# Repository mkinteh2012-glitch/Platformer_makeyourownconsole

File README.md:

# Pixel Player 8
Overview    
This is a console made and designed by @PenguinMo or Muhammad Kinteh for Hack Club's build your own console program 
This repo is organized into 5 sections.  
0. Overview
1. Pixel Platformer
2. Console Controller
3. Console Launcher
4. Console Design

Pixel Platformer 

Embark on an epic quest . . .     
This is pixel platformer a game designed in Godot 4 for the console, Pixel Player 8 this game is a platformer based off brackeye's tutorial 
You can play the game here: https://muhammad12412.itch.io/pixel-platformer 
Watch the walkthrough here: https://www.youtube.com/watch?v=EgpC5o8dRrM 
Screenshots:

2. Controller

So now u can play!        
This is a controller made by me and powered by the
This controller has the same layout as an Xbox 1 except no center button  
Screenshots: 

3. Launcher
The launcher for this is very simple it uses python and has good capabilities and is controller and arrow key compatable
This was made for .exe games making it possible to add other non godot games, Screenshots:     

4. Console
The console is povered by a mini PC and put is a case layout it hase foam for protection and holes can be cut in the case it hase speakers and everything needed

TIME BREAKDOWN: Game: 13h via hackatime Controller 14h via journal launcher 8 via hackatime Console 27 via journal Total: 60hx 5 = 300

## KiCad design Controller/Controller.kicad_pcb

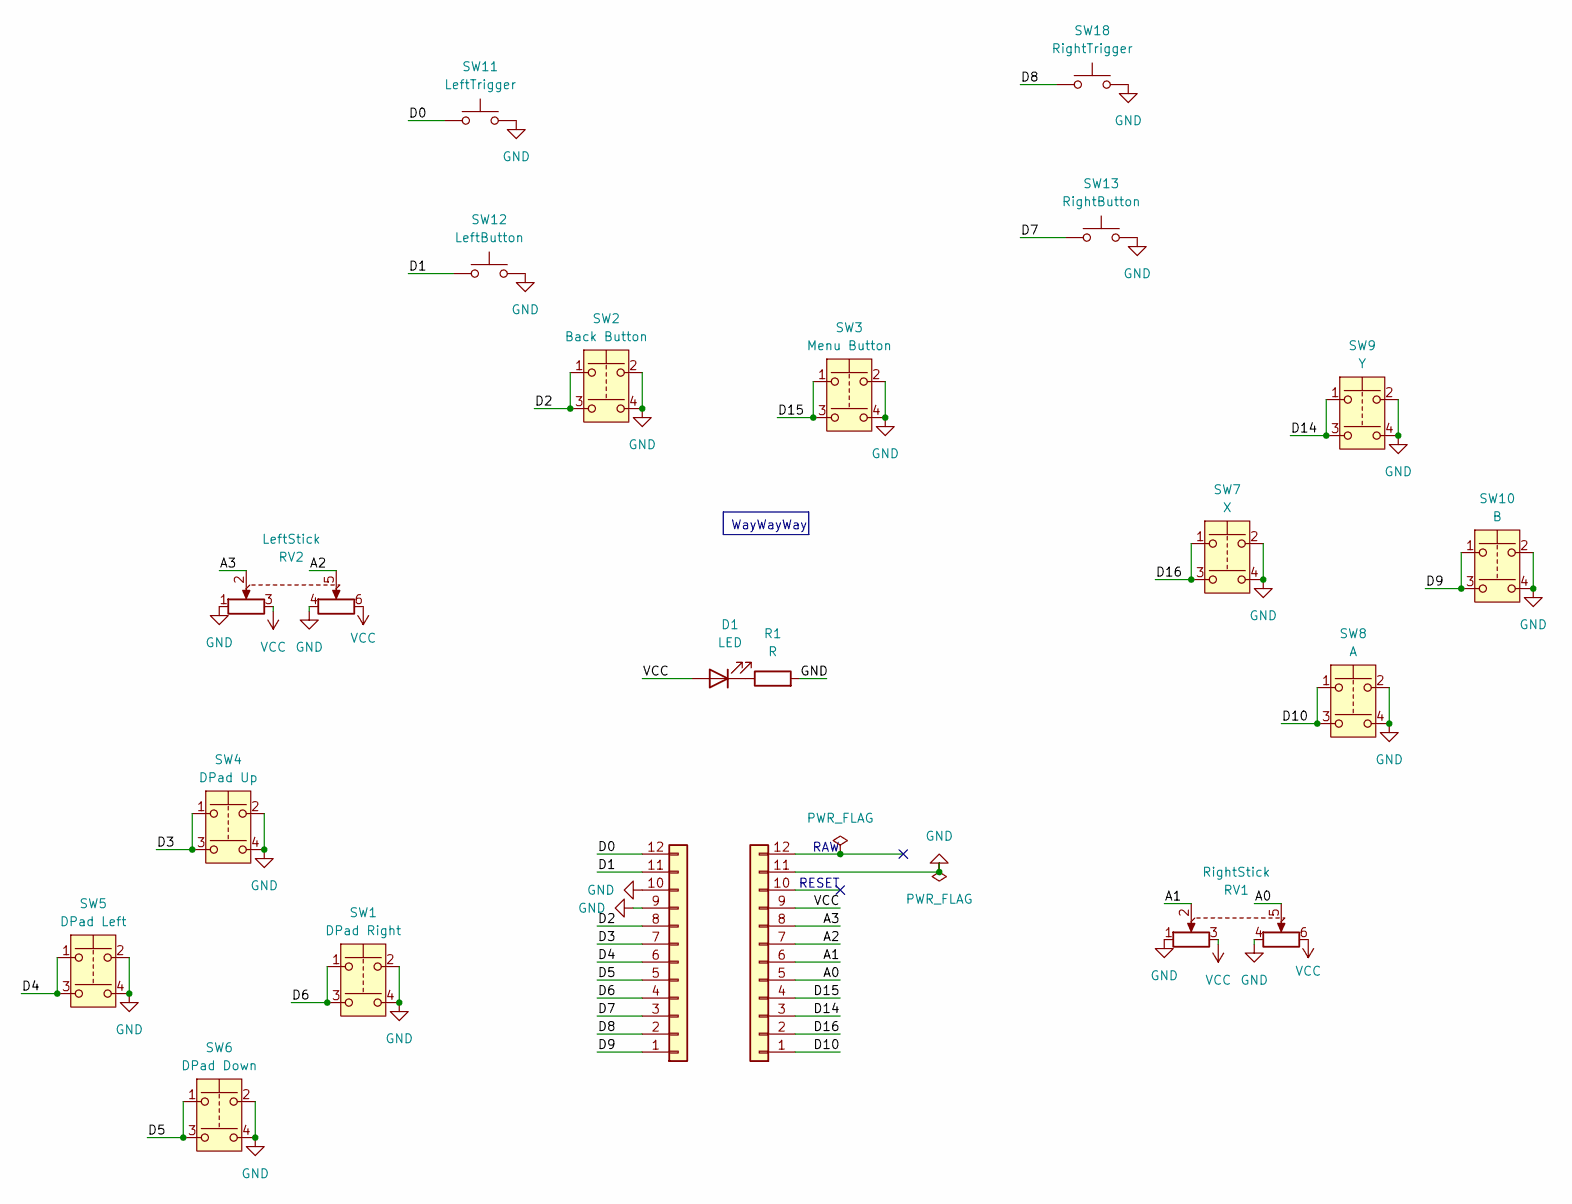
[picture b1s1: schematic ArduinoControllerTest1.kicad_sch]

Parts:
D1: LED; LED_D5.0mm
J3, J4: Conn_01x12; PinHeader_1x12_P2.54mm_Vertical
R1: R; R_Axial_DIN0207_L6.3mm_D2.5mm_P10.16mm_Horizontal
RV1: RightStick; JOYSTICK
RV2: LeftStick; JOYSTICK
SW1: DPad Right; Push_E-Switch_KS01Q01
SW2: Back Button; Push_E-Switch_KS01Q01
SW3: Menu Button; Push_E-Switch_KS01Q01
SW4: DPad Up; Push_E-Switch_KS01Q01
SW5: DPad Left; Push_E-Switch_KS01Q01
SW6: DPad Down; Push_E-Switch_KS01Q01
SW7: X; Push_E-Switch_KS01Q01
SW8: A; Push_E-Switch_KS01Q01
SW9: Y; Push_E-Switch_KS01Q01
SW10: B; Push_E-Switch_KS01Q01
SW11: LeftTrigger; SW_Tactile_SKHH_Angled
SW12: LeftButton; SW_Tactile_SKHH_Angled
SW13: RightButton; SW_Tactile_SKHH_Angled
SW18: RightTrigger; SW_Tactile_SKHH_Angled

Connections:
/A0: J3.5, RV1.5
/A1: J3.6, RV1.2
/A2: J3.7, RV2.5
/A3: J3.8, RV2.2
/D0: J4.12, SW11.1
/D1: J4.11, SW12.1
/D2: J4.8, SW2.1, SW2.3
/D3: J4.7, SW4.1, SW4.3
/D4: J4.6, SW5.1, SW5.3
/D5: J4.5, SW6.1, SW6.3
/D6: J4.4, SW1.1, SW1.3
/D7: J4.3, SW13.1
/D8: J4.2, SW18.1
/D9: J4.1, SW10.1, SW10.3
/D10: J3.1, SW8.1, SW8.3
/D14: J3.3, SW9.1, SW9.3
/D15: J3.4, SW3.1, SW3.3
/D16: J3.2, SW7.1, SW7.3
GND: J3.11, J4.9, J4.10, R1.2, RV1.1, RV1.4, RV2.1, RV2.4, SW1.2, SW1.4, SW2.2, SW2.4, SW3.2, SW3.4, SW4.2, SW4.4, SW5.2, SW5.4, SW6.2, SW6.4, SW7.2, SW7.4, SW8.2, SW8.4, SW9.2, SW9.4, SW10.2, SW10.4, SW11.2, SW12.2, SW13.2, SW18.2
unnamed: D1.1 (K), R1.1
VCC: D1.2 (A), J3.9, RV1.3, RV1.6, RV2.3, RV2.6

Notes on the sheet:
WayWayWay
RAW
RESET

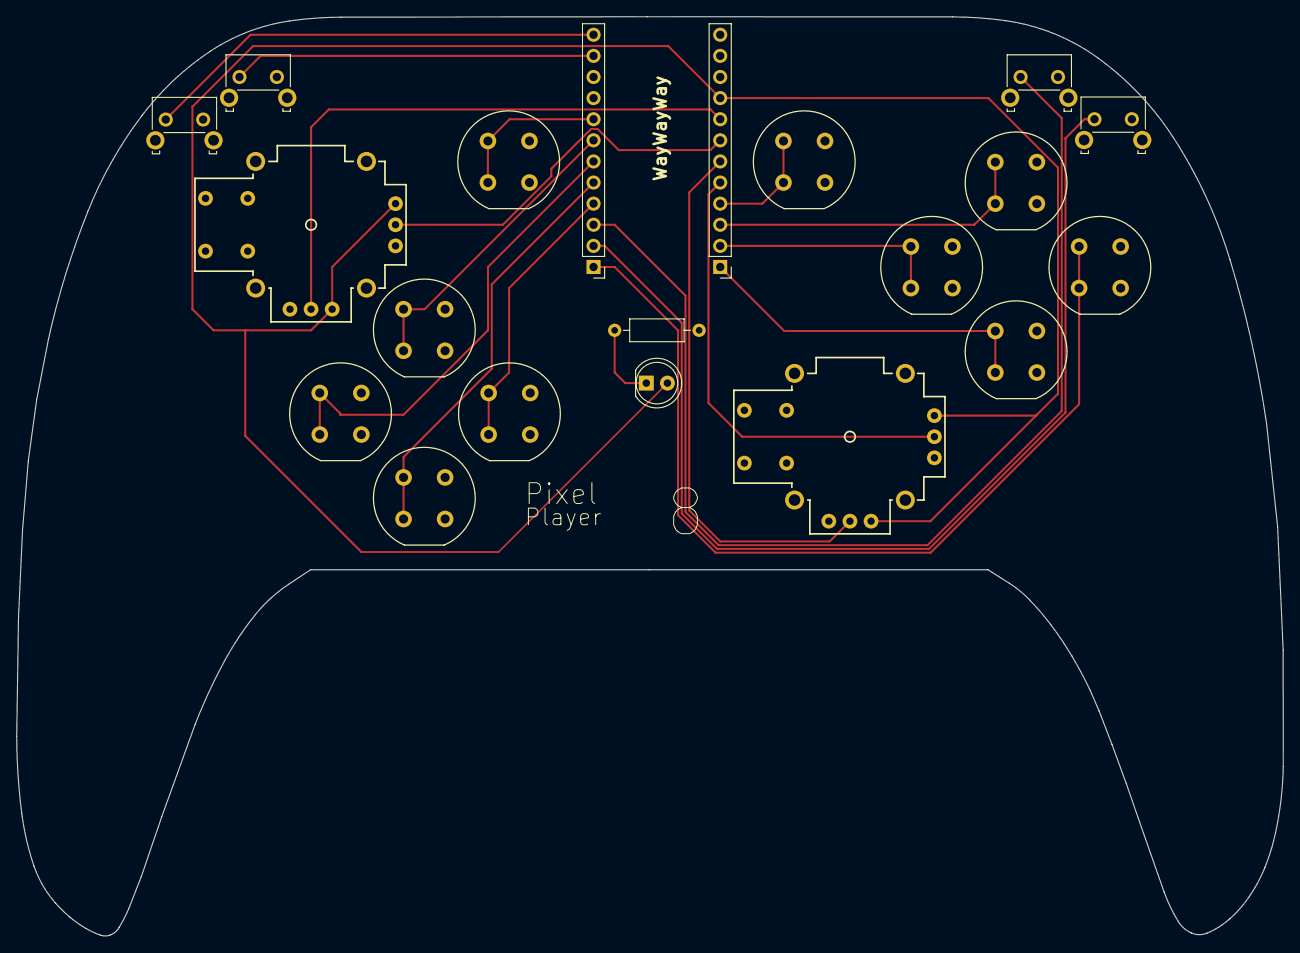
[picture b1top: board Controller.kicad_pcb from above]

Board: 2 copper layers, 152.4 x 110.6 mm, 20 parts (0 on the bottom side), 21 nets.

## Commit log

2026-01-08 Started added basic physics
2026-01-08 Organized project into Game folder
2026-01-08 Organized all project folders into Game directory
2026-01-08 Cleanup: Move metadata to root
2026-01-08 Began level design
2026-01-08 Added platform
2026-01-10 fixed death
2026-01-10 added slime
2026-01-10 added player animation
2026-01-11 added more level
2026-01-11 added more coins
2026-01-11 added bg
2026-01-12 now there is checkpints
2026-01-12 DONE
2026-01-12 Rename Console Game to Pixel Platformer
    Updated the README to reflect the new game title and added details about the Pixel Platformer.
2026-01-15 Revise README with project name and sections
    Updated README to include project name and details.
2026-01-15 Add journal entry on console design concept
    Added a new entry about console design ideas.
2026-01-17 Update Journal with project ideas and progress
    Added detailed entries about project progress and plans.
2026-01-17 Revise journal entry with PCB design details
    Updated the journal entry to include details about the exposed PCB design.
2026-01-17 Rename Controller/Controller.kicad_pro to Controller/KICAD/Controller.kicad_pro
2026-01-17 Rename ArduinoControllerTest1.kicad_sch to Controller.kicad_sch
2026-01-18 Add main.py for XInput controller setup and loop
2026-01-18 Update Journal with recent project progress
    Added new journal entries detailing the progress on schematic, PCB, firmware, and BOM.
2026-01-18 Add screenshots to README
    Added screenshots to the README for better visualization.
2026-01-18 Fix typo in Journal.md entry
2026-01-18 Update README with new screenshots
    Added additional images to the README for better visualization.
2026-01-18 Update CONTROLLERBOM.csv with new items and prices
2026-01-18 Correct console name in README
    Updated the console name in the game description.
2026-01-26 ADDED THE FIRMWARE ENTRY
2026-01-29 Rename ConsoleJournal.md to Console/ConsoleJournal.md
